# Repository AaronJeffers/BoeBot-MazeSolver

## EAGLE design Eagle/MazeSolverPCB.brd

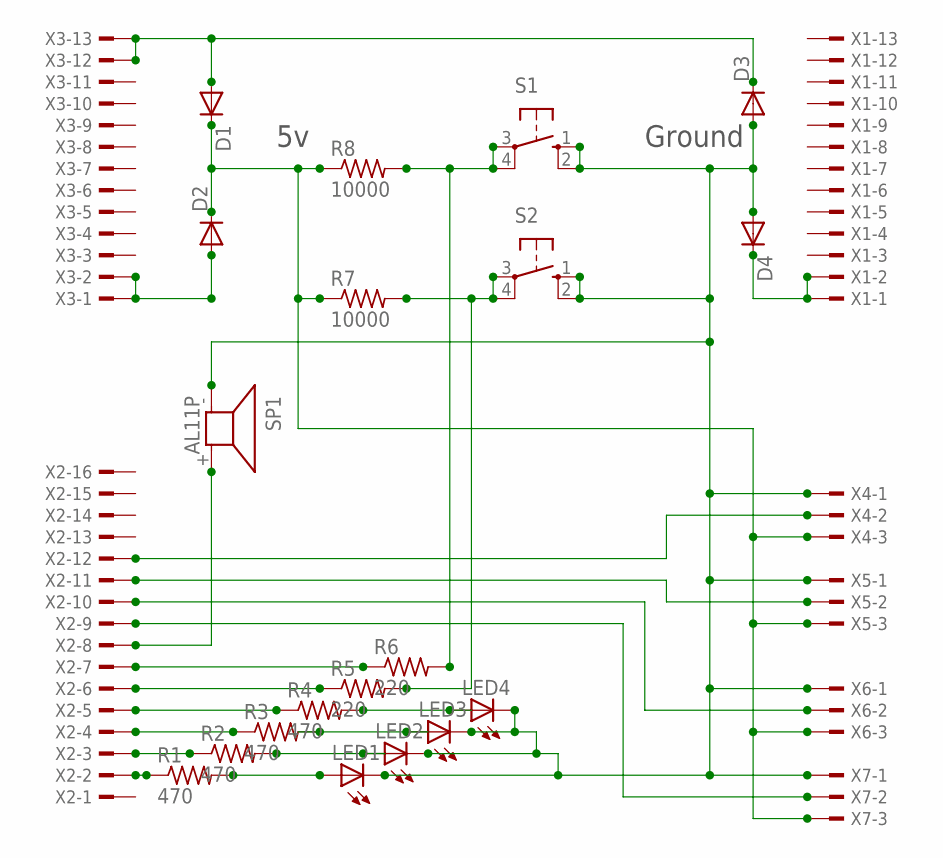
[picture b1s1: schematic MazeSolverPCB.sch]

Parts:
D1, D2, D3, D4: 1N4004; DO41-10
LED1, LED2, LED3, LED4: TLLG4400; LED3MM
R1, R2, R3, R4: 470; 0207/7
R5, R6: 220; 0207/7
R7, R8: 10000; 0207/7
S1, S2: 10-XX; B3F-10XX
SP1: AL11P
X1, X3: TSW-113-02-S-S
X2: TSW-116-02-S-S
X4, X5, X6, X7: TSW-103-02-S-S

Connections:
unnamed: D3.A, D4.A, LED1.K (C), LED2.K (C), LED3.K (C), LED4.K (C), S1.1 (S), S1.2 (S1), S2.1 (S), S2.2 (S1), SP1.- (1), X4.1, X5.1, X6.1, X7.1
unnamed: D1.C, D2.C, R7.1, R8.1, X4.3, X5.3, X6.3, X7.3
unnamed: SP1.+ (2), X2.8
unnamed: X2.12, X4.2
unnamed: LED1.A, R1.2
unnamed: R3.1, X2.4
unnamed: X2.11, X5.2
unnamed: D4.C, X1.1, X1.2
unnamed: R2.1, X2.3
unnamed: R1.1, X2.2
unnamed: X2.10, X6.2
unnamed: R5.2, R7.2, S2.3, S2.4 (P1)
unnamed: R6.2, R8.2, S1.3, S1.4 (P1)
unnamed: X2.9, X7.2
unnamed: D2.A, X3.1, X3.2
unnamed: D1.A, D3.C, X3.12, X3.13
unnamed: R4.1, X2.5
unnamed: R5.1, X2.6
unnamed: R6.1, X2.7
unnamed: LED4.A, R4.2
unnamed: LED3.A, R3.2
unnamed: LED2.A, R2.2

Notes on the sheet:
Ground

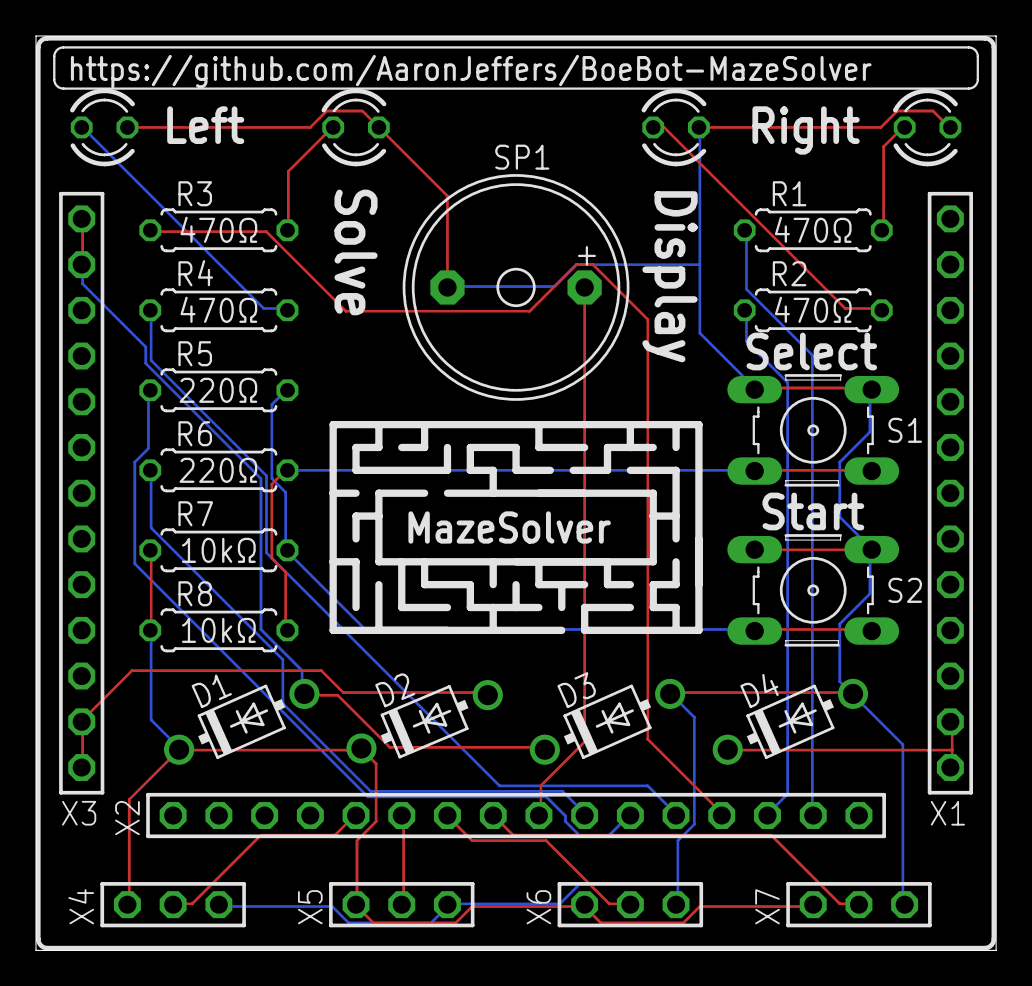
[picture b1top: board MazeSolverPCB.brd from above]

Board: 2 copper layers, 53.3 x 50.8 mm, 26 parts (0 on the bottom side), 22 nets.

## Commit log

2016-01-18 Moved files in
2016-01-18 Renamed files
2016-09-21 Added arduino write to EEprom
2016-09-22 Added read to EEPROM
2016-09-22 Added read EEPROM
2016-09-22 Fixed Eagle routing.
2016-10-01 Fixed Resistor values and folder names
2016-10-01 Added LEDs
2016-10-03 Added comments
2016-10-03 Added .gitignore
2016-10-04 Changed Autorouting
2016-10-06 Added eclipse workspace
2016-11-22 Fixed LED issue
